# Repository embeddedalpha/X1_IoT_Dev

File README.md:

# Wi-Fi & LoRA enabled Security Node  

### Check out GrabCAD for STEP Model: https://grabcad.com/library/home-surveillance-node-v1-1
### With generous help from JLCPCB. Check them out on jlcpcb.com

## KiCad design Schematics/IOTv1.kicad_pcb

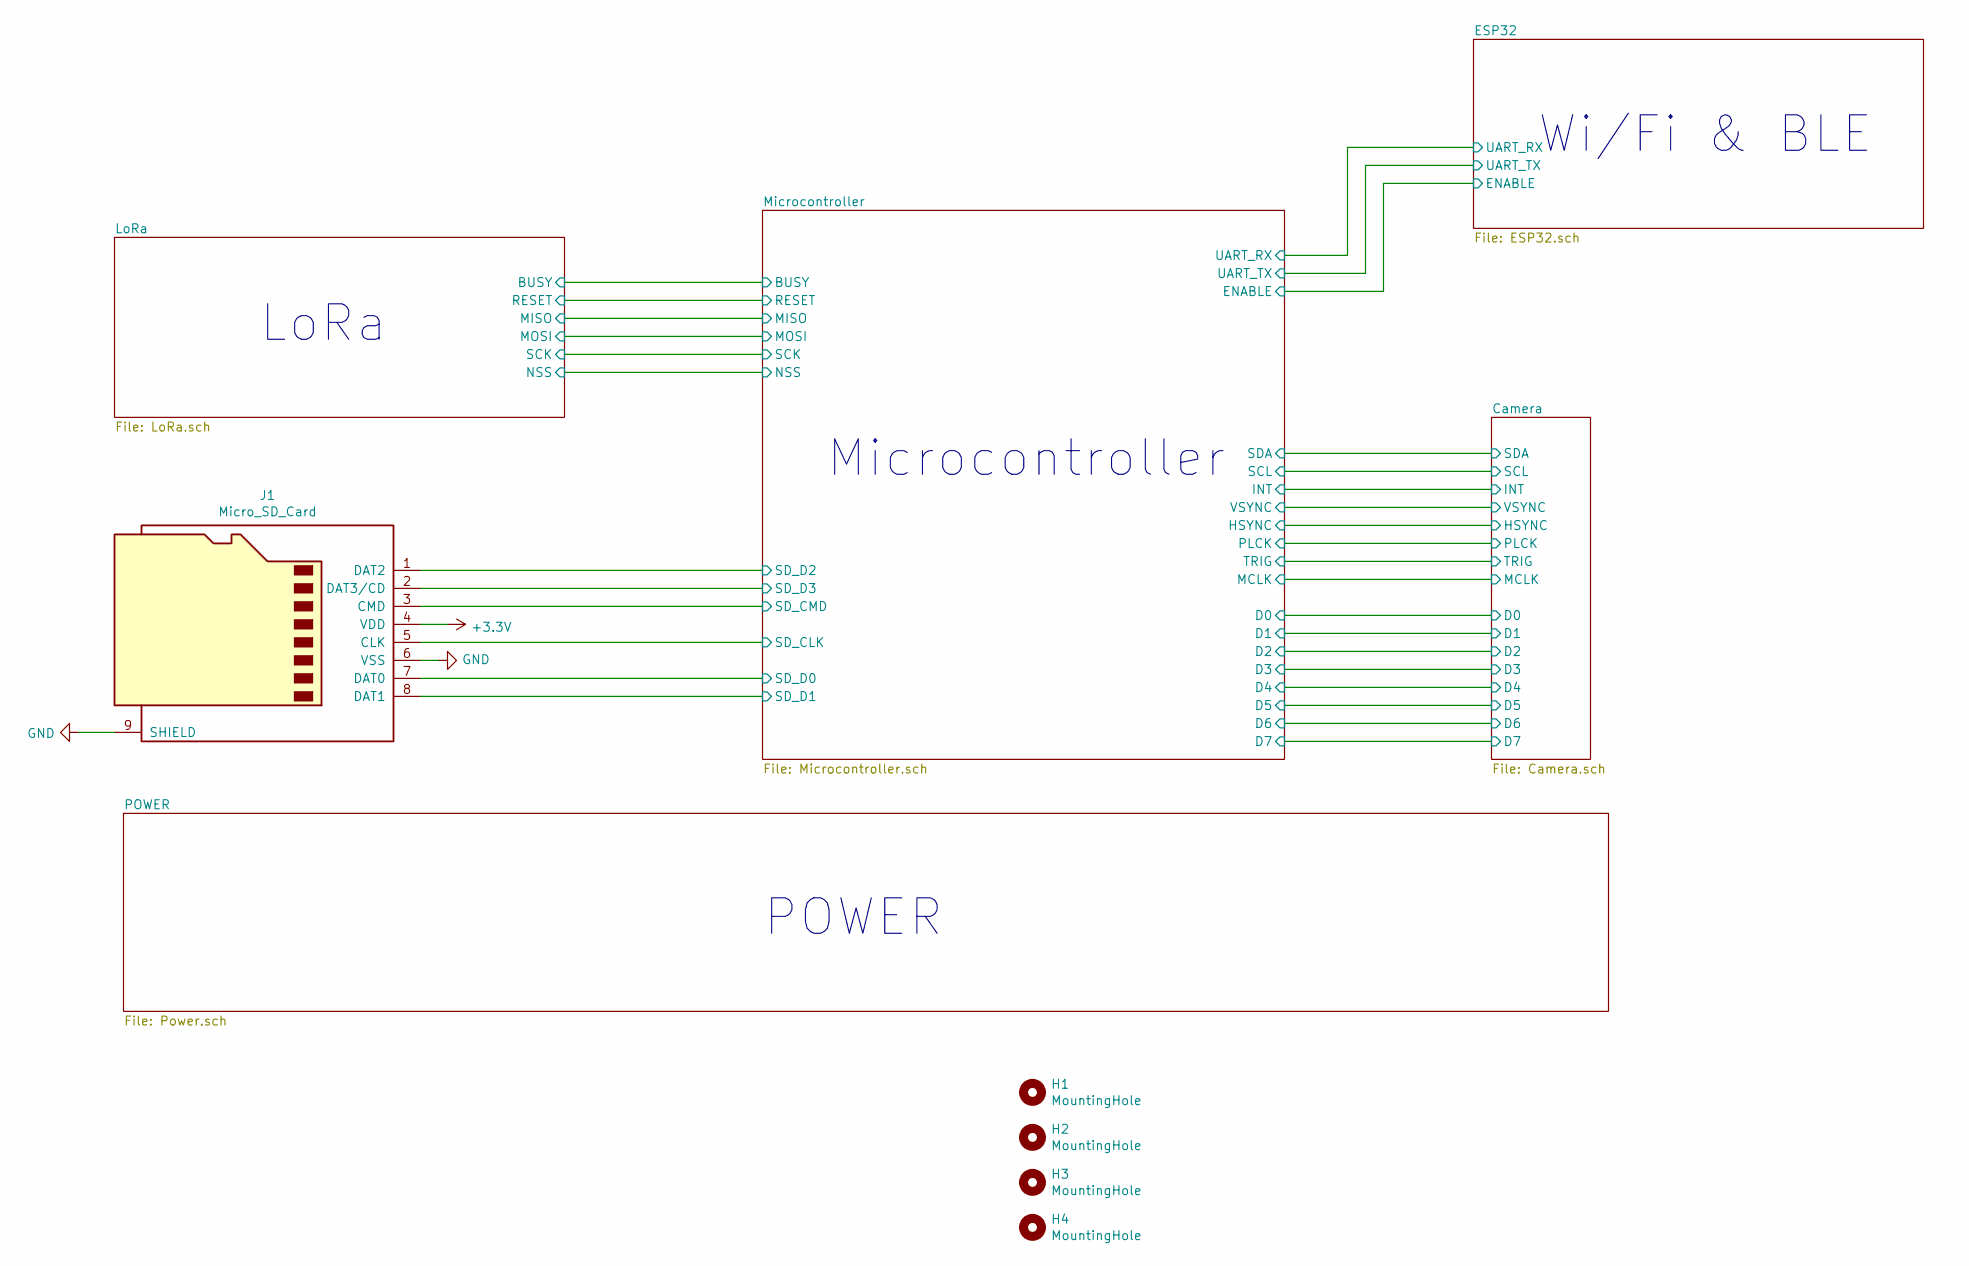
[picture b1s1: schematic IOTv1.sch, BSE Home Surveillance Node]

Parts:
H1, H2, H3, H4: MountingHole; MountingHole_3.2mm_M3_ISO7380_Pad
J1: Micro_SD_Card; microSD_HC_Wuerth_693072010801

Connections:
+3V3: J1.4 (VDD); also elsewhere on the board
/Microcontroller/SD_CLK: J1.5 (CLK); also elsewhere on the board
/Microcontroller/SD_CMD: J1.3 (CMD); also elsewhere on the board
/Microcontroller/SD_D0: J1.7 (DAT0); also elsewhere on the board
/Microcontroller/SD_D1: J1.8 (DAT1); also elsewhere on the board
/Microcontroller/SD_D2: J1.1 (DAT2); also elsewhere on the board
/Microcontroller/SD_D3: J1.2 (DAT3/CD); also elsewhere on the board
GND: J1.6 (VSS), J1.9 (SHIELD); also elsewhere on the board

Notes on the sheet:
POWER
Microcontroller
LoRa
Wi/Fi & BLE

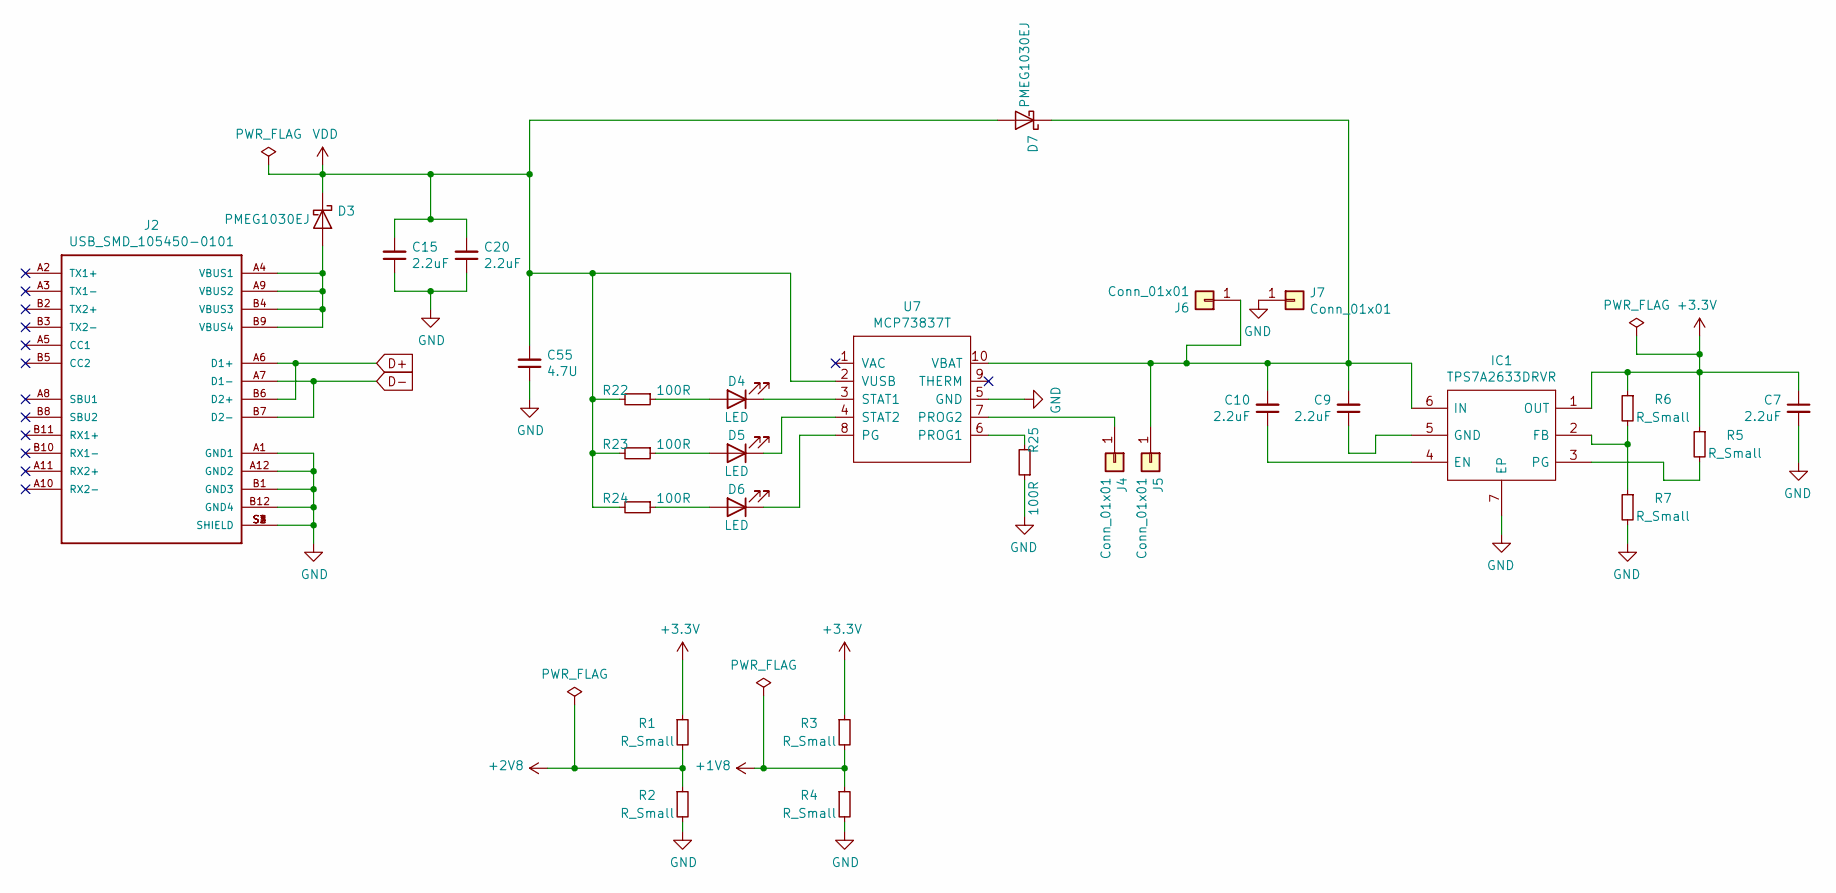
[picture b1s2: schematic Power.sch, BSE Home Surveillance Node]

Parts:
C7, C9, C10, C15, C20: 2.2uF; C_0402_1005Metric
C55: 4.7U; C_0402_1005Metric
D3, D7: PMEG1030EJ; D_SOD-323F
D4, D5, D6: LED; LED_0402_1005Metric
IC1: TPS7A2633DRVR; Mouser Part Number 595-TPS7A2633DRVR
J2: USB_SMD_105450-0101; MOLEX_105450-0101
J4, J5, J6, J7: Conn_01x01; 2.54MM PIN
R1, R2, R3, R4, R5, R6, R7: R_Small; R_0402_1005Metric
R22, R23, R24, R25: 100R; R_0402_1005Metric
U7: MCP73837T; DFN-10-1EP_3x3mm_P0.5mm_EP1.55x2.48mm

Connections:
+1V8: R3.2, R4.1; also elsewhere on the board
+2V8: R1.2, R2.1; also elsewhere on the board
+3V3: C7.1, IC1.1 (OUT), R1.1, R3.1, R5.1, R6.1; also elsewhere on the board
D+: J2.A6 (D1+), J2.B6 (D2+); also elsewhere on the board
D-: J2.A7 (D1-), J2.B7 (D2-); also elsewhere on the board
GND: C7.2, C15.1, C20.1, C55.1, IC1.7 (EP), J2.A1 (GND1), J2.A12 (GND2), J2.B1 (GND3), J2.B12 (GND4), J2.S1 (SHIELD), J2.S2 (SHIELD), J2.S3 (SHIELD), J2.S4 (SHIELD), J7.1, R2.2, R4.2, R7.2, R25.1, U7.5 (GND); also elsewhere on the board
unnamed: C9.1, IC1.5 (GND)
unnamed: C10.1, IC1.4 (EN)
unnamed: C9.2, C10.2, D7.1 (K), IC1.6 (IN), J5.1, J6.1, U7.10 (VBAT)
unnamed: D3.2 (A), J2.A4 (VBUS1), J2.A9 (VBUS2), J2.B4 (VBUS3), J2.B9 (VBUS4)
unnamed: D4.1 (K), U7.3 (STAT1)
unnamed: D4.2 (A), R22.1
unnamed: D5.1 (K), U7.4 (STAT2)
unnamed: D5.2 (A), R23.1
unnamed: D6.1 (K), U7.8 (PG)
unnamed: D6.2 (A), R24.1
unnamed: IC1.2 (FB), R6.2, R7.1
unnamed: IC1.3 (PG), R5.2
unnamed: J4.1, U7.7 (PROG2)
unnamed: R25.2, U7.6 (PROG1)
VDD: C15.2, C20.2, C55.2, D3.1 (K), D7.2 (A), R22.2, R23.2, R24.2, U7.2 (VUSB); also elsewhere on the board

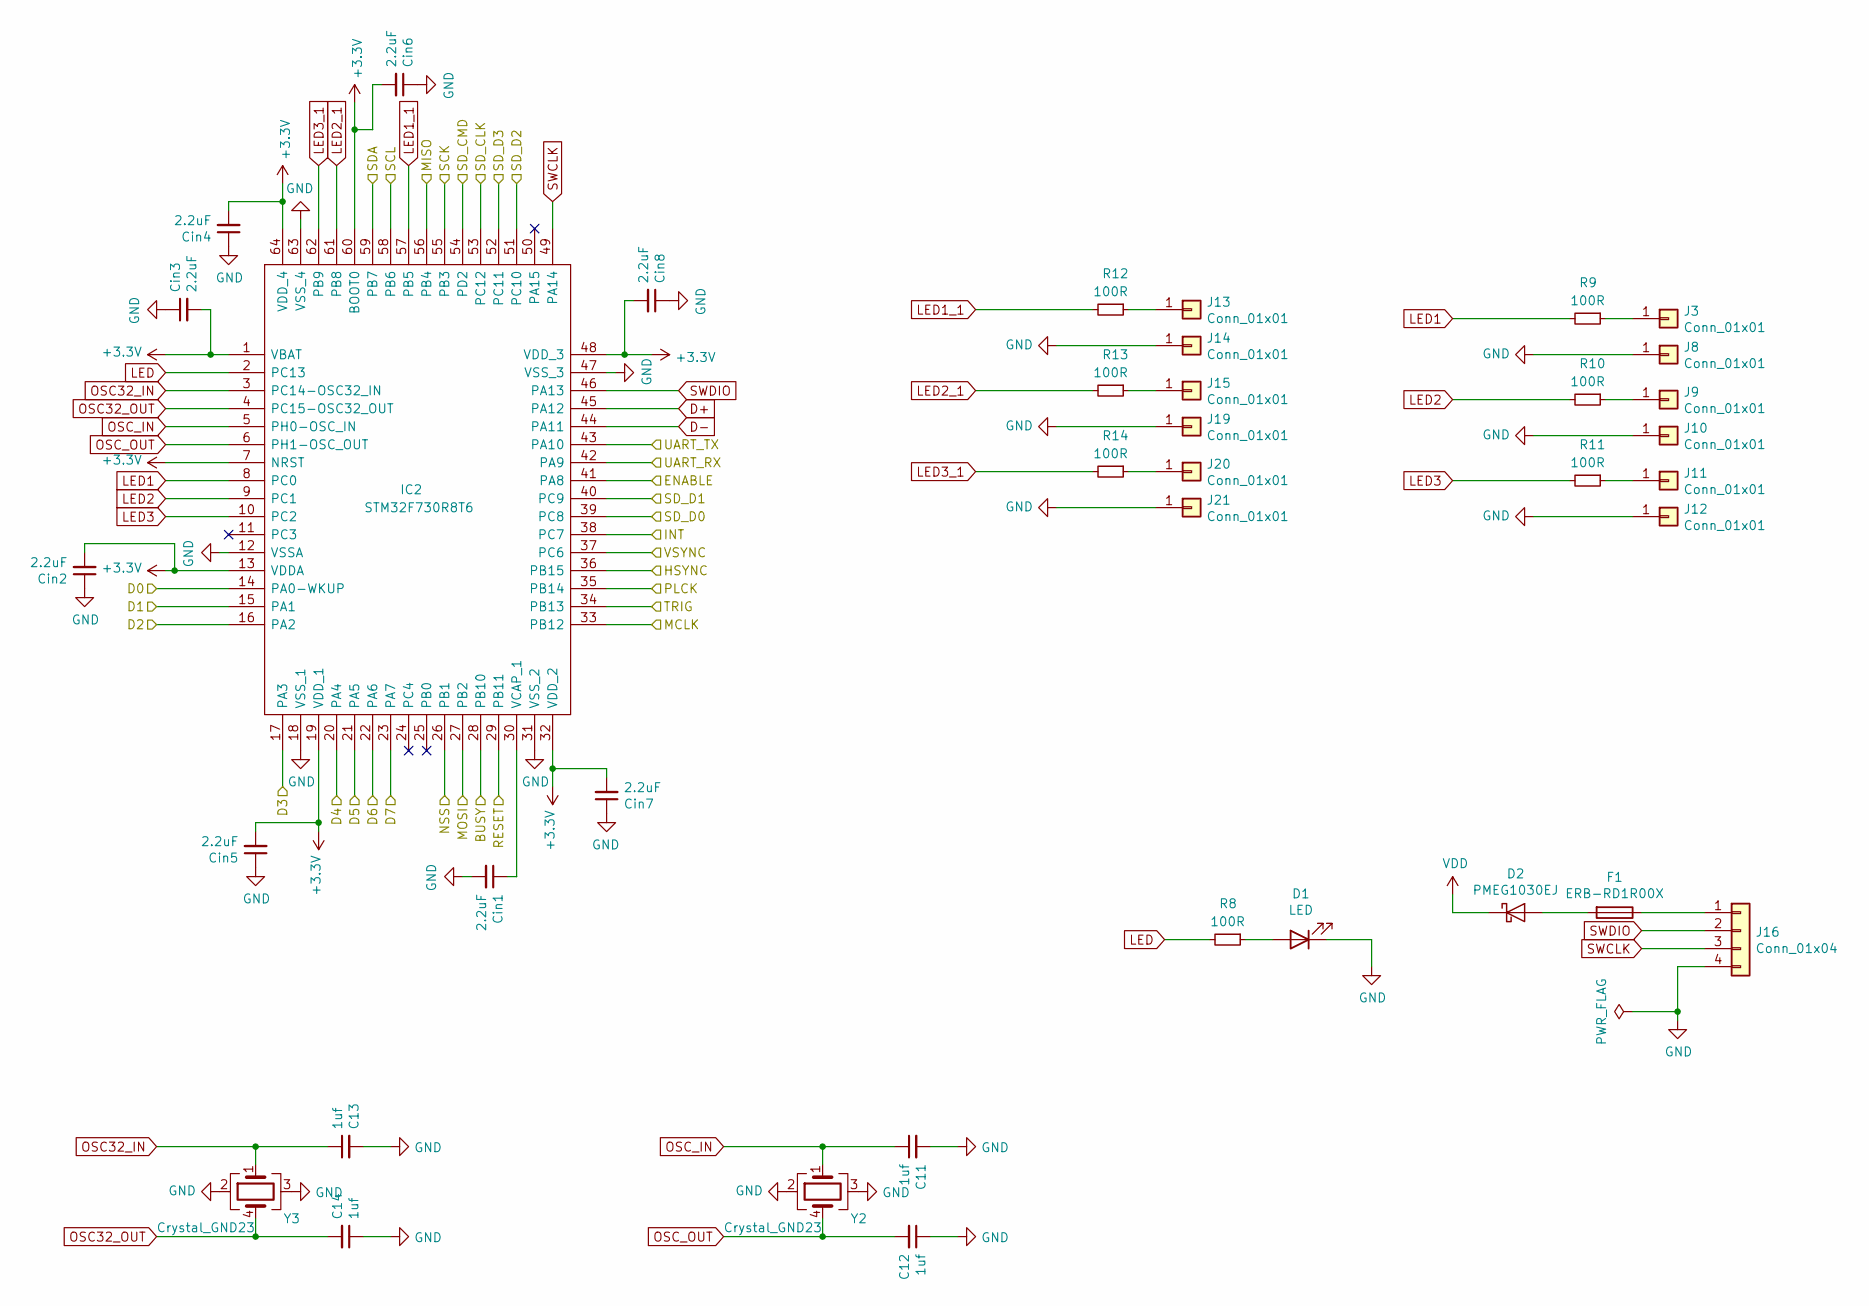
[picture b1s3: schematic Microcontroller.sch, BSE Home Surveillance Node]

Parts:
C11, C12, C13, C14: 1uf; C_0402_1005Metric
Cin1, Cin2, Cin3, Cin4, Cin5, Cin6, Cin7, Cin8: 2.2uF; C_0402_1005Metric
D1: LED; LED_0402_1005Metric
D2: PMEG1030EJ; D_SOD-323F
F1: ERB-RD1R00X; Fuse_0402_1005Metric
IC2: STM32F730R8T6; QFP50P1200X1200X160-64N; Mouser Part Number 511-STM32F730R8T6
J3, J8, J9, J10, J11, J12, J13, J14, J15, J19, J20, J21: Conn_01x01; 2.54MM PIN
J16: Conn_01x04; SWD_PINS
R8, R9, R10, R11, R12, R13, R14: 100R; R_0402_1005Metric
Y2: Crystal_GND23; Crystal_SMD_SeikoEpson_FA238V-4Pin_3.2x2.5mm
Y3: Crystal_GND23; Crystal_SMD_SeikoEpson_MA406-4Pin_11.7x4.0mm

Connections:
+3V3: Cin2.2, Cin3.2, Cin4.2, Cin5.2, Cin6.2, Cin7.2, Cin8.2, IC2.1 (VBAT), IC2.7 (NRST), IC2.13 (VDDA), IC2.19 (VDD_1), IC2.32 (VDD_2), IC2.48 (VDD_3), IC2.60 (BOOT0), IC2.64 (VDD_4); also elsewhere on the board
/Camera/D0: IC2.14 (PA0-WKUP); also elsewhere on the board
/Camera/D1: IC2.15 (PA1); also elsewhere on the board
/Camera/D2: IC2.16 (PA2); also elsewhere on the board
/Camera/D3: IC2.17 (PA3); also elsewhere on the board
/Camera/D4: IC2.20 (PA4); also elsewhere on the board
/Camera/D5: IC2.21 (PA5); also elsewhere on the board
/Camera/D6: IC2.22 (PA6); also elsewhere on the board
/Camera/D7: IC2.23 (PA7); also elsewhere on the board
/Camera/HSYNC: IC2.36 (PB15); also elsewhere on the board
/Camera/INT: IC2.38 (PC7); also elsewhere on the board
/Camera/MCLK: IC2.33 (PB12); also elsewhere on the board
/Camera/PLCK: IC2.35 (PB14); also elsewhere on the board
/Camera/SCL: IC2.58 (PB6); also elsewhere on the board
/Camera/SDA: IC2.59 (PB7); also elsewhere on the board
/Camera/TRIG: IC2.34 (PB13); also elsewhere on the board
/Camera/VSYNC: IC2.37 (PC6); also elsewhere on the board
/ESP32/ENABLE: IC2.41 (PA8); also elsewhere on the board
/ESP32/UART_RX: IC2.42 (PA9); also elsewhere on the board
/ESP32/UART_TX: IC2.43 (PA10); also elsewhere on the board
/LoRa/BUSY: IC2.28 (PB10); also elsewhere on the board
/LoRa/MISO: IC2.56 (PB4); also elsewhere on the board
/LoRa/MOSI: IC2.27 (PB2); also elsewhere on the board
/LoRa/NSS: IC2.26 (PB1); also elsewhere on the board
/LoRa/RESET: IC2.29 (PB11); also elsewhere on the board
/LoRa/SCK: IC2.55 (PB3); also elsewhere on the board
/Microcontroller/SD_CLK: IC2.53 (PC12); also elsewhere on the board
/Microcontroller/SD_CMD: IC2.54 (PD2); also elsewhere on the board
/Microcontroller/SD_D0: IC2.39 (PC8); also elsewhere on the board
/Microcontroller/SD_D1: IC2.40 (PC9); also elsewhere on the board
/Microcontroller/SD_D2: IC2.51 (PC10); also elsewhere on the board
/Microcontroller/SD_D3: IC2.52 (PC11); also elsewhere on the board
D+: IC2.45 (PA12); also elsewhere on the board
D-: IC2.44 (PA11); also elsewhere on the board
GND: C11.2, C12.1, C13.2, C14.1, Cin1.2, Cin2.1, Cin3.1, Cin4.1, Cin5.1, Cin6.1, Cin7.1, Cin8.1, D1.1 (K), IC2.12 (VSSA), IC2.18 (VSS_1), IC2.31 (VSS_2), IC2.47 (VSS_3), IC2.63 (VSS_4), J8.1, J10.1, J12.1, J14.1, J16.4, J19.1, J21.1, Y2.2, Y2.3, Y3.2, Y3.3; also elsewhere on the board
LED: IC2.2 (PC13), R8.2
LED1: IC2.8 (PC0), R9.2
LED1_1: IC2.57 (PB5), R12.2
LED2: IC2.9 (PC1), R10.2
LED2_1: IC2.61 (PB8), R13.2
LED3: IC2.10 (PC2), R11.2
LED3_1: IC2.62 (PB9), R14.2
unnamed: Cin1.1, IC2.30 (VCAP_1)
unnamed: D1.2 (A), R8.1
unnamed: D2.2 (A), F1.2
unnamed: F1.1, J16.1
unnamed: J3.1, R9.1
unnamed: J9.1, R10.1
unnamed: J11.1, R11.1
unnamed: J13.1, R12.1
unnamed: J15.1, R13.1
unnamed: J20.1, R14.1
OSC32_IN: C13.1, IC2.3 (PC14-OSC32_IN), Y3.1
OSC32_OUT: C14.2, IC2.4 (PC15-OSC32_OUT), Y3.4
OSC_IN: C11.1, IC2.5 (PH0-OSC_IN), Y2.1
OSC_OUT: C12.2, IC2.6 (PH1-OSC_OUT), Y2.4
SWCLK: IC2.49 (PA14), J16.3
SWDIO: IC2.46 (PA13), J16.2
VDD: D2.1 (K); also elsewhere on the board

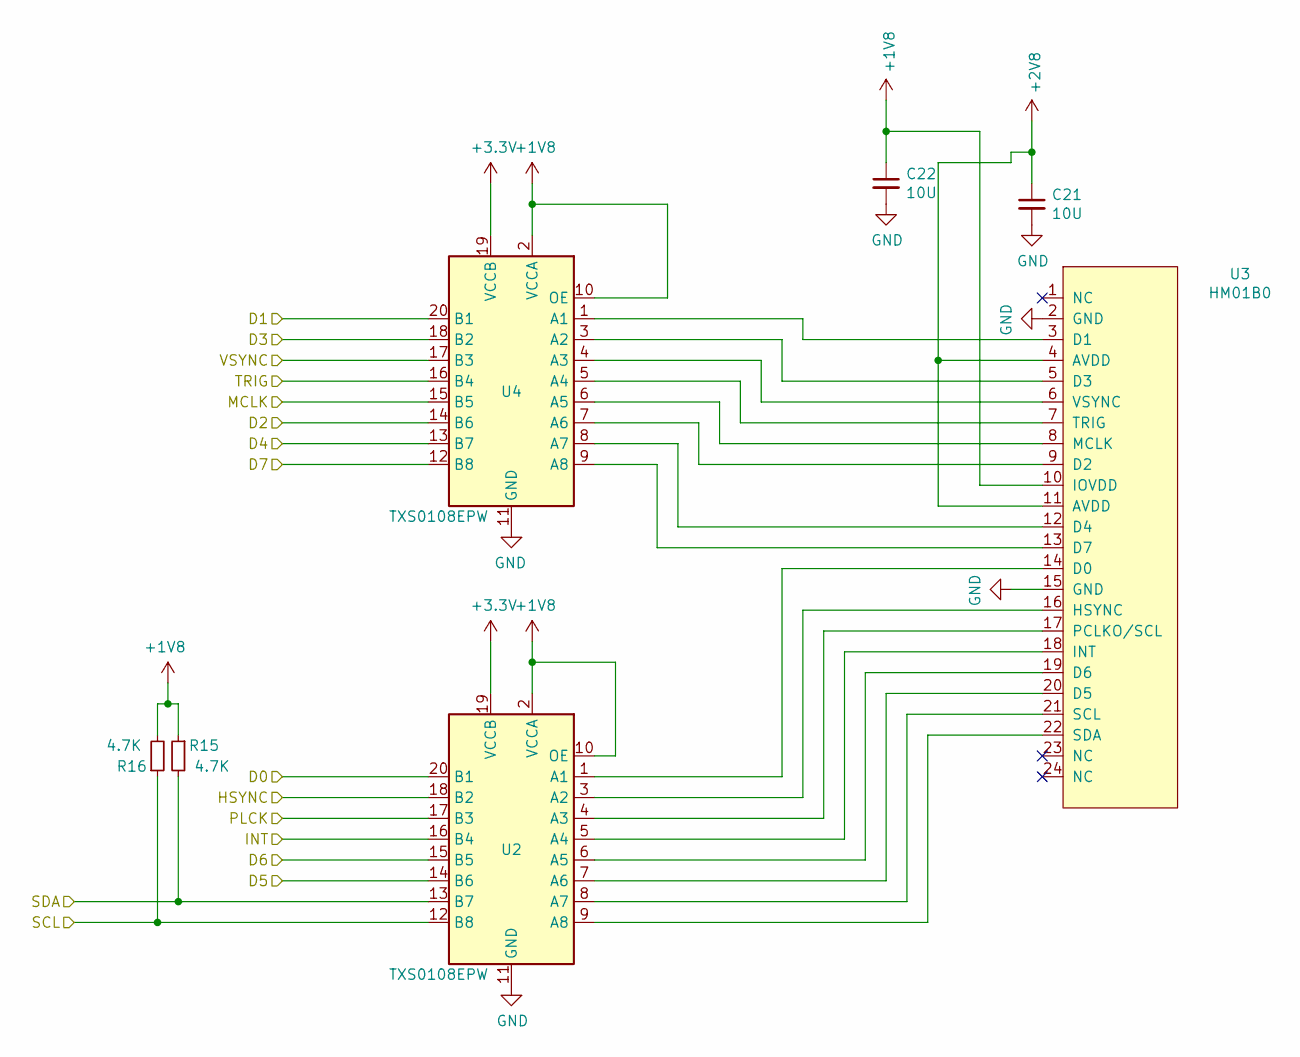
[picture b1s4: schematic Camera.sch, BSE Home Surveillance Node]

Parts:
C21, C22: 10U; C_0402_1005Metric
R15, R16: 4.7K; R_0402_1005Metric
U2, U4: TXS0108EPW; TSSOP-20_4.4x6.5mm_P0.65mm
U3: HM01B0

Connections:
+1V8: C22.1, R15.1, R16.2, U2.2 (VCCA), U2.10 (OE), U3.10 (IOVDD), U4.2 (VCCA), U4.10 (OE); also elsewhere on the board
+2V8: C21.1, U3.4 (AVDD), U3.11 (AVDD); also elsewhere on the board
+3V3: U2.19 (VCCB), U4.19 (VCCB); also elsewhere on the board
/Camera/D0: U2.20 (B1); also elsewhere on the board
/Camera/D1: U4.20 (B1); also elsewhere on the board
/Camera/D2: U4.14 (B6); also elsewhere on the board
/Camera/D3: U4.18 (B2); also elsewhere on the board
/Camera/D4: U4.13 (B7); also elsewhere on the board
/Camera/D5: U2.14 (B6); also elsewhere on the board
/Camera/D6: U2.15 (B5); also elsewhere on the board
/Camera/D7: U4.12 (B8); also elsewhere on the board
/Camera/HSYNC: U2.18 (B2); also elsewhere on the board
/Camera/INT: U2.16 (B4); also elsewhere on the board
/Camera/MCLK: U4.15 (B5); also elsewhere on the board
/Camera/PLCK: U2.17 (B3); also elsewhere on the board
/Camera/SCL: R16.1, U2.12 (B8); also elsewhere on the board
/Camera/SDA: R15.2, U2.13 (B7); also elsewhere on the board
/Camera/TRIG: U4.16 (B4); also elsewhere on the board
/Camera/VSYNC: U4.17 (B3); also elsewhere on the board
GND: C21.2, C22.2, U2.11 (GND), U3.2 (GND), U3.15 (GND), U4.11 (GND); also elsewhere on the board
unnamed: U2.1 (A1), U3.14 (D0)
unnamed: U2.3 (A2), U3.16 (HSYNC)
unnamed: U2.4 (A3), U3.17 (PCLKO/SCL)
unnamed: U2.5 (A4), U3.18 (INT)
unnamed: U2.6 (A5), U3.19 (D6)
unnamed: U2.7 (A6), U3.20 (D5)
unnamed: U2.8 (A7), U3.21 (SCL)
unnamed: U2.9 (A8), U3.22 (SDA)
unnamed: U3.3 (D1), U4.1 (A1)
unnamed: U3.5 (D3), U4.3 (A2)
unnamed: U3.6 (VSYNC), U4.4 (A3)
unnamed: U3.7 (TRIG), U4.5 (A4)
unnamed: U3.8 (MCLK), U4.6 (A5)
unnamed: U3.9 (D2), U4.7 (A6)
unnamed: U3.12 (D4), U4.8 (A7)
unnamed: U3.13 (D7), U4.9 (A8)

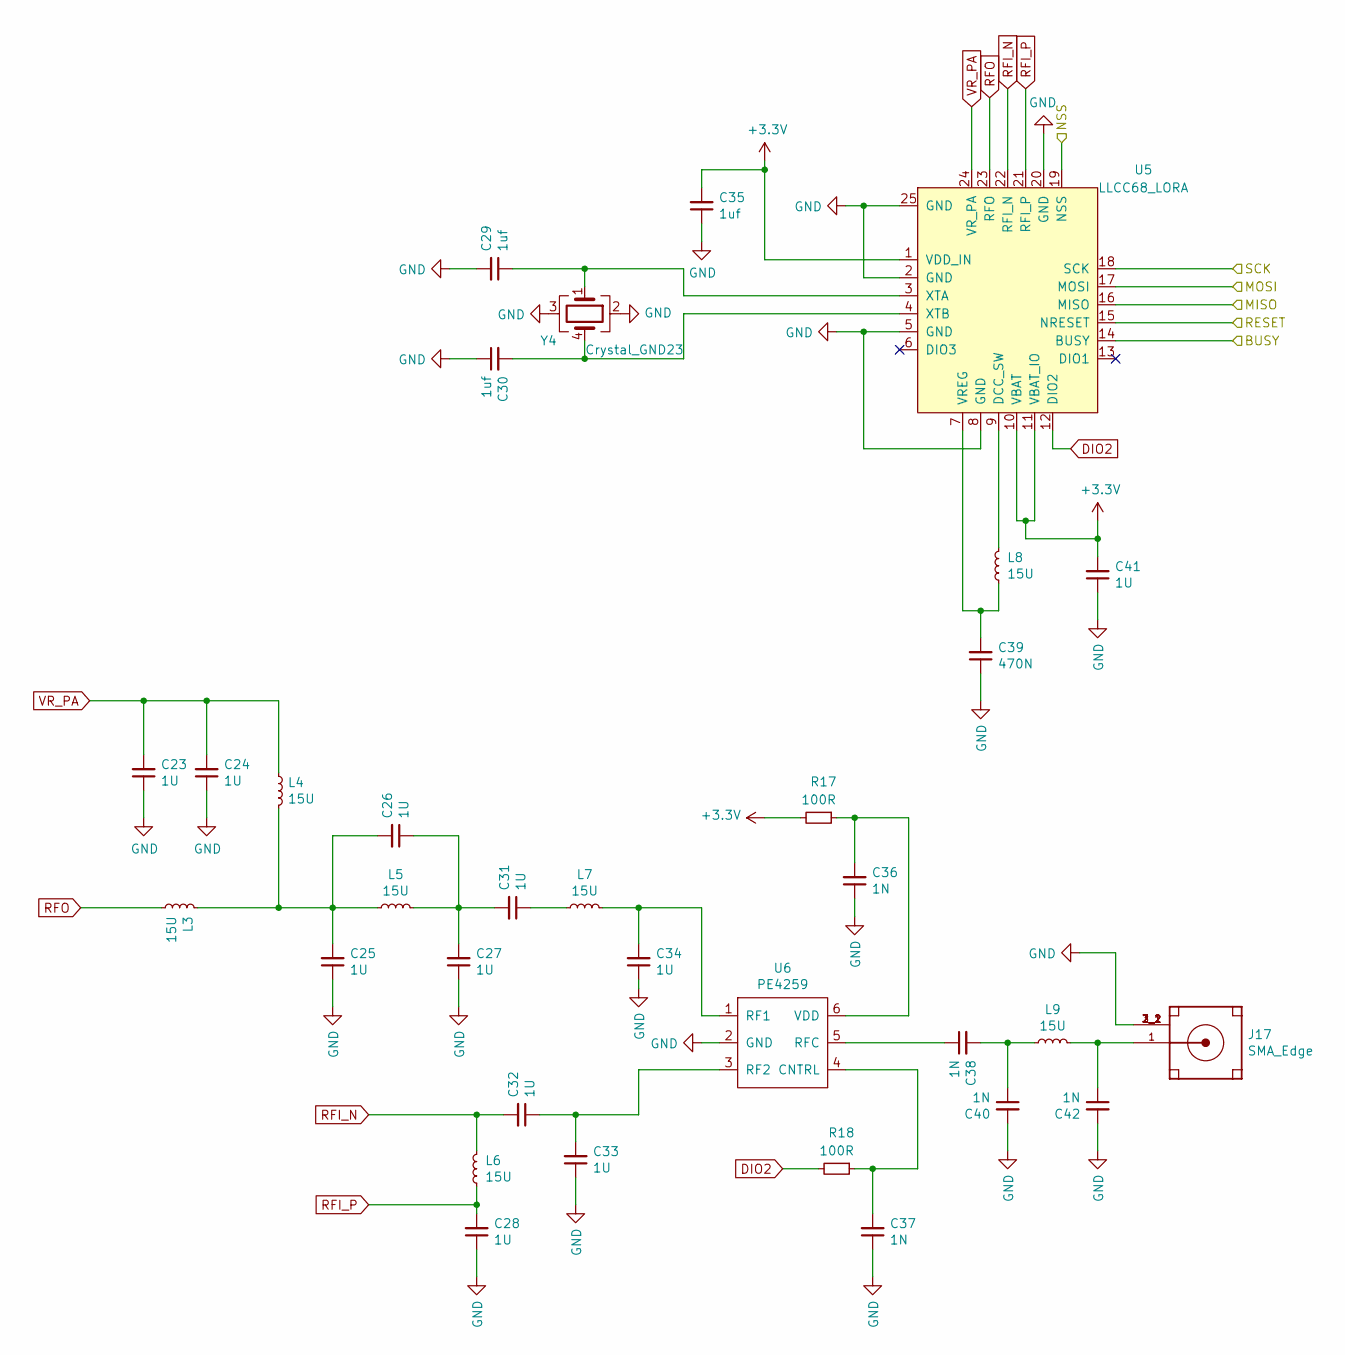
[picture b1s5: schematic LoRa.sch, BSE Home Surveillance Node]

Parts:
C23, C24, C25, C26, C27, C28, C31, C32, C33, C34, C41: 1U; C_0402_1005Metric
C29, C30, C35: 1uf; C_0402_1005Metric
C36, C37, C38, C40, C42: 1N; C_0402_1005Metric
C39: 470N; C_0402_1005Metric
J17: SMA_Edge; SMA-J-P-H-ST-EM1
L3, L4, L5, L6, L7, L8, L9: 15U; L_0402_1005Metric
R17, R18: 100R; R_0402_1005Metric
U5: LLCC68_LORA; QFN-24-1EP_4x4mm_P0.5mm_EP2.6x2.6mm
U6: PE4259; SOT65P215X110-6N
Y4: Crystal_GND23; Crystal_SMD_SeikoEpson_FA238V-4Pin_3.2x2.5mm

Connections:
+3V3: C35.2, C41.2, R17.2, U5.1 (VDD_IN), U5.10 (VBAT), U5.11 (VBAT_IO); also elsewhere on the board
/LoRa/BUSY: U5.14 (BUSY); also elsewhere on the board
/LoRa/MISO: U5.16 (MISO); also elsewhere on the board
/LoRa/MOSI: U5.17 (MOSI); also elsewhere on the board
/LoRa/NSS: U5.19 (NSS); also elsewhere on the board
/LoRa/RESET: U5.15 (NRESET); also elsewhere on the board
/LoRa/SCK: U5.18 (SCK); also elsewhere on the board
DIO2: R18.2, U5.12 (DIO2)
GND: C23.1, C24.1, C25.1, C27.1, C28.1, C29.2, C30.1, C33.1, C34.1, C35.1, C36.1, C37.1, C39.1, C40.2, C41.1, C42.2, J17.2_1 (GND), J17.2_2 (GND), J17.3_1 (GND), J17.3_2 (GND), U5.2 (GND), U5.5 (GND), U5.8 (GND), U5.20 (GND), U5.25 (GND), U6.2 (GND), Y4.2, Y4.3; also elsewhere on the board
unnamed: C25.2, C26.2, L3.2, L4.2, L5.1
unnamed: C26.1, C27.2, C31.2, L5.2
unnamed: C29.1, U5.3 (XTA), Y4.1
unnamed: C30.2, U5.4 (XTB), Y4.4
unnamed: C31.1, L7.1
unnamed: C32.1, C33.2, U6.3 (RF2)
unnamed: C34.2, L7.2, U6.1 (RF1)
unnamed: C36.2, R17.1, U6.6 (VDD)
unnamed: C37.2, R18.1, U6.4 (CNTRL)
unnamed: C38.1, U6.5 (RFC)
unnamed: C38.2, C40.1, L9.1
unnamed: C39.2, L8.1, U5.7 (VREG)
unnamed: C42.1, J17.1 (SIGNAL), L9.2
unnamed: L8.2, U5.9 (DCC_SW)
RFI_N: C32.2, L6.2, U5.22 (RFI_N)
RFI_P: C28.2, L6.1, U5.21 (RFI_P)
RFO: L3.1, U5.23 (RFO)
VR_PA: C23.2, C24.2, L4.1, U5.24 (VR_PA)

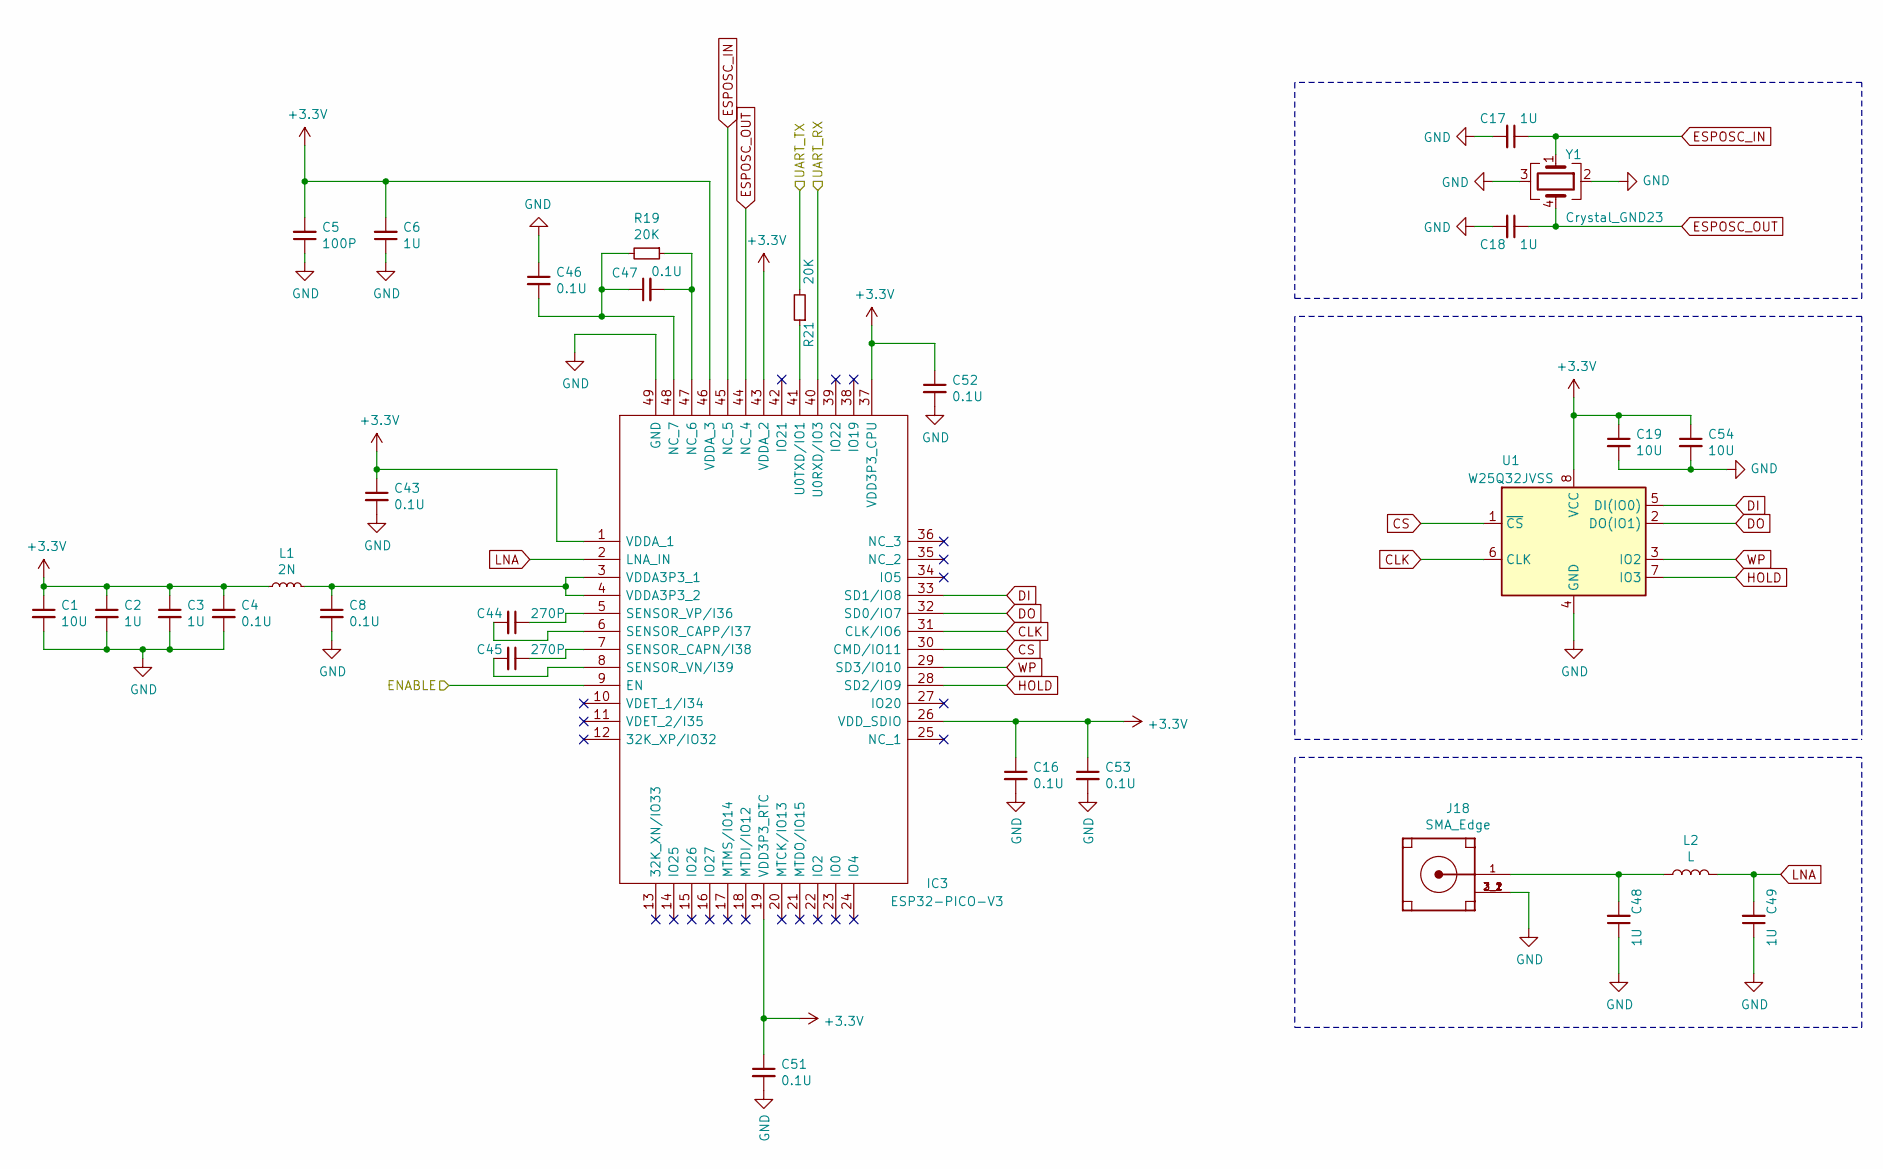
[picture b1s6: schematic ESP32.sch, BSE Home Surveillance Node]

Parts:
C1, C19, C54: 10U; C_0402_1005Metric
C2, C3, C6, C17, C18, C48, C49: 1U; C_0402_1005Metric
C4, C8, C16, C43, C46, C47, C51, C52, C53: 0.1U; C_0402_1005Metric
C5: 100P; C_0402_1005Metric
C44, C45: 270P; C_0402_1005Metric
IC3: ESP32-PICO-V3; ESP32PICOV3; Mouser Part Number 356-ESP32-PICO-V3
J18: SMA_Edge; SMA-J-P-H-ST-EM1
L1: 2N; L_0402_1005Metric
L2: L; L_0402_1005Metric
R19, R21: 20K; R_0402_1005Metric
U1: W25Q32JVSS; SOIC-8_5.23x5.23mm_P1.27mm
Y1: Crystal_GND23; Crystal_SMD_TXC_7M-4Pin_3.2x2.5mm

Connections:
+3V3: C1.1, C2.1, C3.1, C4.1, C5.2, C6.2, C16.1, C19.1, C43.1, C51.1, C52.1, C53.1, C54.1, IC3.1 (VDDA_1), IC3.19 (VDD3P3_RTC), IC3.26 (VDD_SDIO), IC3.37 (VDD3P3_CPU), IC3.43 (VDDA_2), IC3.46 (VDDA_3), L1.1, U1.8 (VCC); also elsewhere on the board
/ESP32/ENABLE: IC3.9 (EN); also elsewhere on the board
/ESP32/UART_RX: IC3.40 (U0RXD/IO3); also elsewhere on the board
/ESP32/UART_TX: R21.2; also elsewhere on the board
CLK: IC3.31 (CLK/IO6), U1.6 (CLK)
CS: IC3.30 (CMD/IO11), U1.1 (~CS)
DI: IC3.33 (SD1/IO8), U1.5 (DI(IO0))
DO: IC3.32 (SD0/IO7), U1.2 (DO(IO1))
ESPOSC_IN: C17.1, IC3.45 (NC_5), Y1.1
ESPOSC_OUT: C18.1, IC3.44 (NC_4), Y1.4
GND: C1.2, C2.2, C3.2, C4.2, C5.1, C6.1, C8.2, C16.2, C17.2, C18.2, C19.2, C43.2, C46.1, C48.1, C49.1, C51.2, C52.2, C53.2, C54.2, IC3.49 (GND), J18.2_1 (GND), J18.2_2 (GND), J18.3_1 (GND), J18.3_2 (GND), U1.4 (GND), Y1.2, Y1.3; also elsewhere on the board
HOLD: IC3.28 (SD2/IO9), U1.7 (IO3)
LNA: C49.2, IC3.2 (LNA_IN), L2.2
unnamed: C8.1, IC3.3 (VDDA3P3_1), IC3.4 (VDDA3P3_2), L1.2
unnamed: C44.1, IC3.5 (SENSOR_VP/I36)
unnamed: C44.2, IC3.6 (SENSOR_CAPP/I37)
unnamed: C45.1, IC3.7 (SENSOR_CAPN/I38)
unnamed: C45.2, IC3.8 (SENSOR_VN/I39)
unnamed: C46.2, C47.1, IC3.48 (NC_7), R19.2
unnamed: C47.2, IC3.47 (NC_6), R19.1
unnamed: C48.2, J18.1 (SIGNAL), L2.1
unnamed: IC3.41 (U0TXD/IO1), R21.1
WP: IC3.29 (SD3/IO10), U1.3 (IO2)

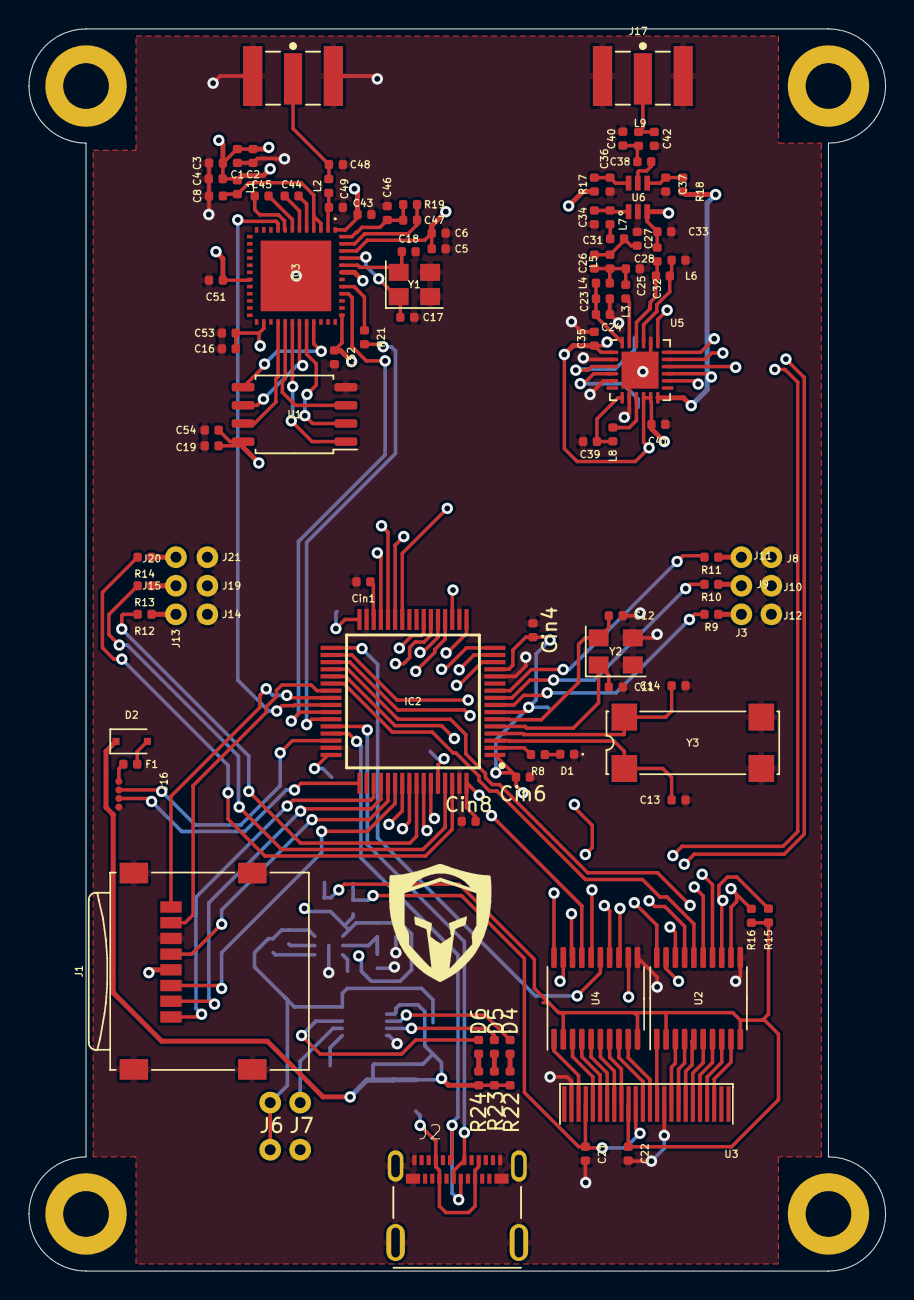
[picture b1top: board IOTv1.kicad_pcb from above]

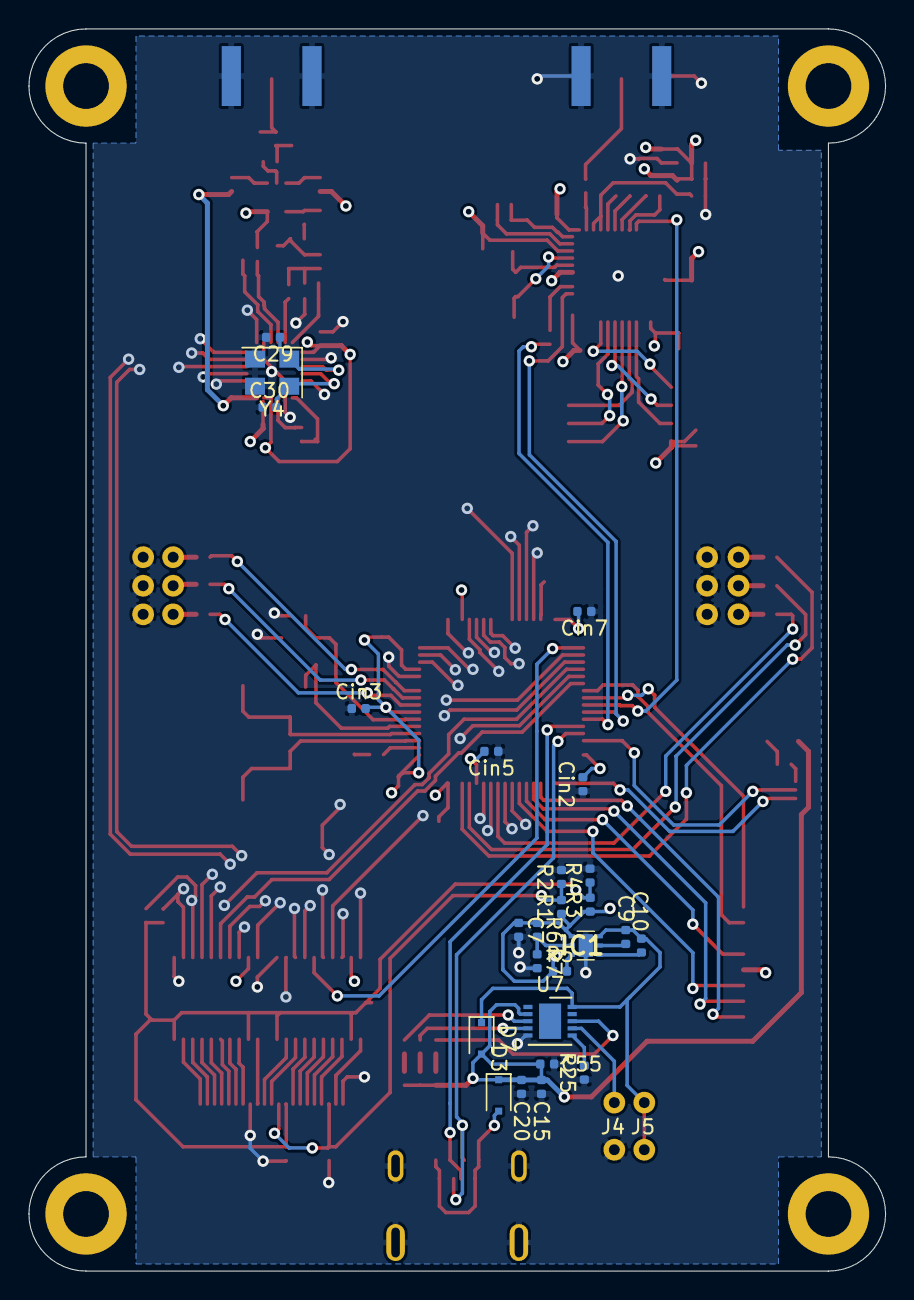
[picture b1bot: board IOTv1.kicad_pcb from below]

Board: 4 copper layers, 60.0 x 87.0 mm, 142 parts (27 on the bottom side), 128 nets.

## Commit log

2020-10-16 Create txt
